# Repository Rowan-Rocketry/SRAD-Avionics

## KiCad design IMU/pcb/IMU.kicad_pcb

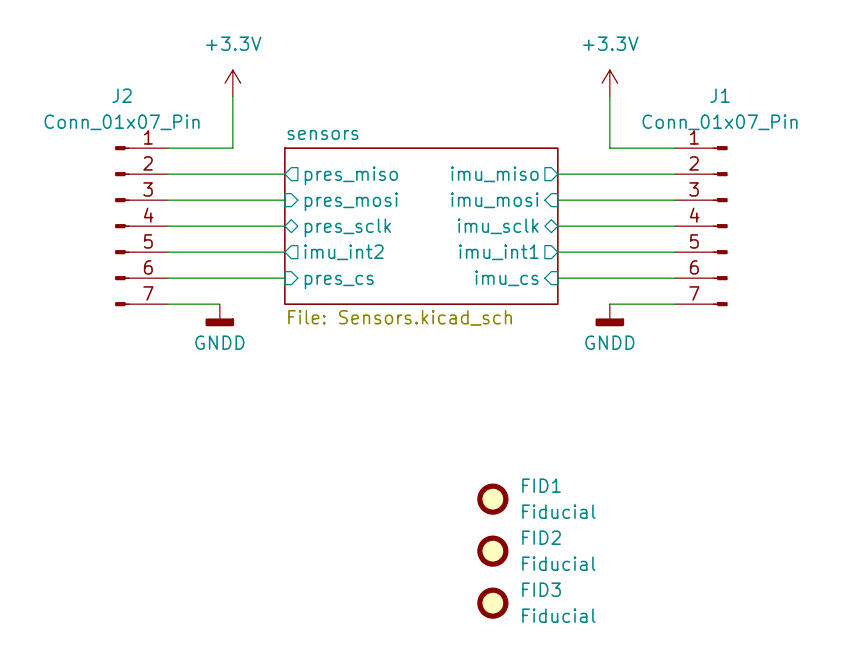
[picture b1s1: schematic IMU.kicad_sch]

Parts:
FID1, FID2, FID3: Fiducial; Fiducial_1mm_Mask2mm
J1, J2: Conn_01x07_Pin; PinHeader_1x07_P2.54mm_Vertical

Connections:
+3.3V: J1.1, J2.1; also elsewhere on the board
/sensors/imu_cs: J1.6; also elsewhere on the board
/sensors/imu_int1: J1.5; also elsewhere on the board
/sensors/imu_int2: J2.5; also elsewhere on the board
/sensors/imu_miso: J1.2; also elsewhere on the board
/sensors/imu_mosi: J1.3; also elsewhere on the board
/sensors/imu_sclk: J1.4; also elsewhere on the board
/sensors/pres_cs: J2.6; also elsewhere on the board
/sensors/pres_miso: J2.2; also elsewhere on the board
/sensors/pres_mosi: J2.3; also elsewhere on the board
/sensors/pres_sclk: J2.4; also elsewhere on the board
GNDD: J1.7, J2.7; also elsewhere on the board

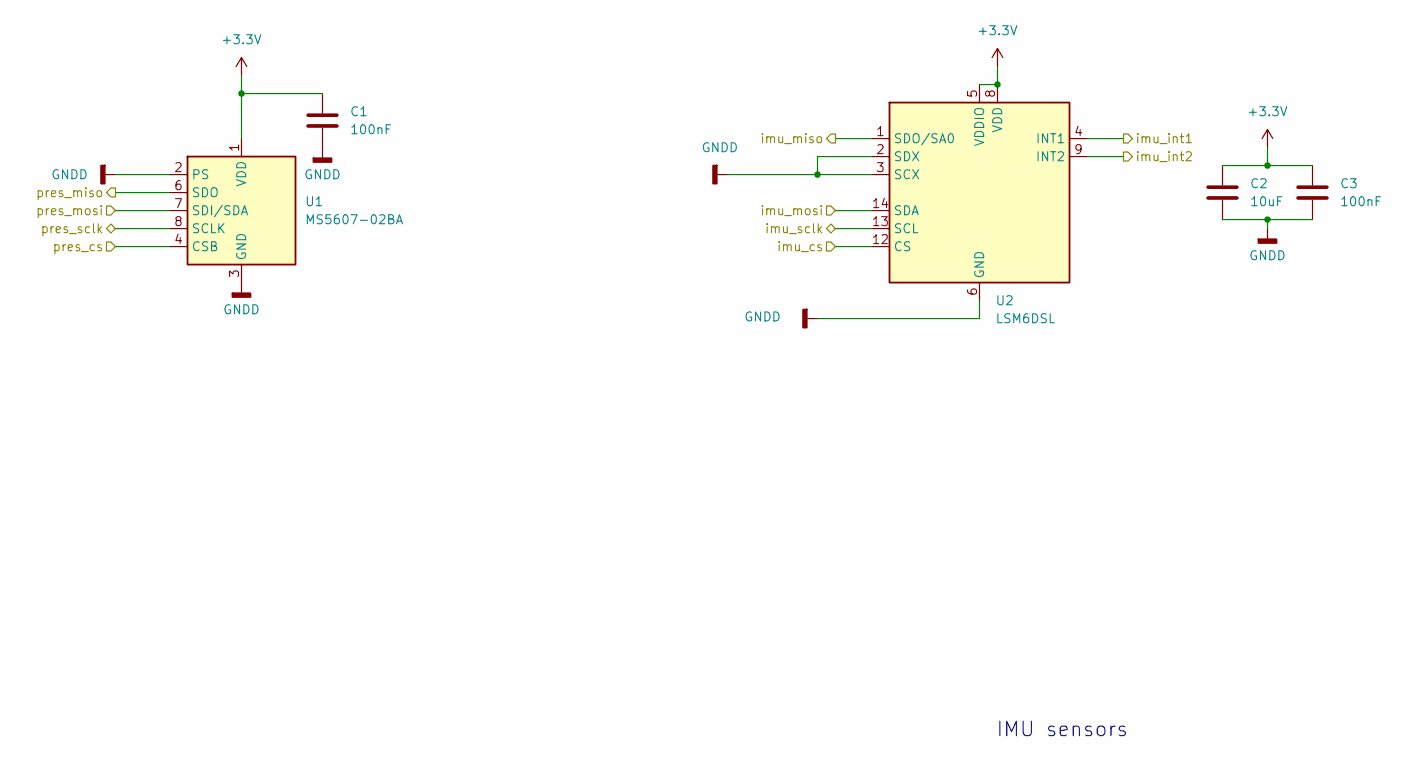
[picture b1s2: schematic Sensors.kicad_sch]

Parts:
C1, C3: 100nF; C_0603_1608Metric_Pad1.08x0.95mm_HandSolder
C2: 10uF; C_0603_1608Metric_Pad1.08x0.95mm_HandSolder
U1: MS5607-02BA; LGA-8_3x5mm_P1.25mm
U2: LSM6DSL; LGA-14_3x2.5mm_P0.5mm_LayoutBorder3x4y

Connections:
+3.3V: C1.1, C2.1, C3.1, U1.1 (VDD), U2.5 (VDDIO), U2.8 (VDD); also elsewhere on the board
/sensors/imu_cs: U2.12 (CS); also elsewhere on the board
/sensors/imu_int1: U2.4 (INT1); also elsewhere on the board
/sensors/imu_int2: U2.9 (INT2); also elsewhere on the board
/sensors/imu_miso: U2.1 (SDO/SA0); also elsewhere on the board
/sensors/imu_mosi: U2.14 (SDA); also elsewhere on the board
/sensors/imu_sclk: U2.13 (SCL); also elsewhere on the board
/sensors/pres_cs: U1.4 (CSB), U1.5 (CSB); also elsewhere on the board
/sensors/pres_miso: U1.6 (SDO); also elsewhere on the board
/sensors/pres_mosi: U1.7 (SDI/SDA); also elsewhere on the board
/sensors/pres_sclk: U1.8 (SCLK); also elsewhere on the board
GNDD: C1.2, C2.2, C3.2, U1.2 (PS), U1.3 (GND), U2.2 (SDX), U2.3 (SCX), U2.6 (GND), U2.7 (GND); also elsewhere on the board

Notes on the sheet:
IMU sensors

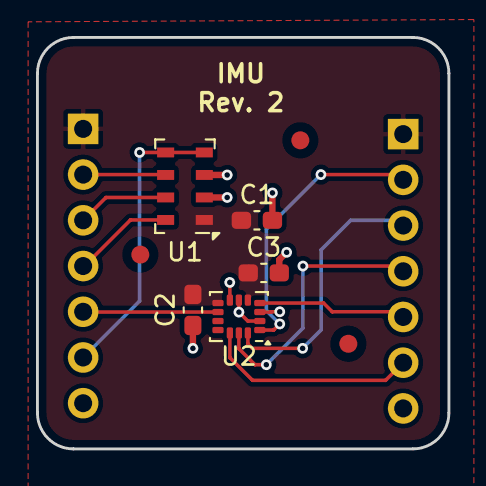
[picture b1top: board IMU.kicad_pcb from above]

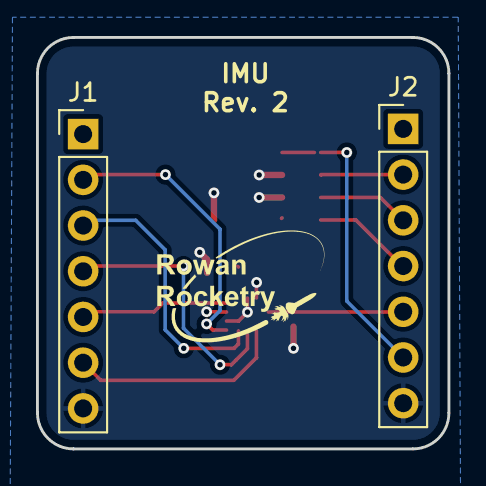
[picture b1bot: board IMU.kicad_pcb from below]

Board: 2 copper layers, 22.9 x 22.9 mm, 10 parts (2 on the bottom side), 12 nets.

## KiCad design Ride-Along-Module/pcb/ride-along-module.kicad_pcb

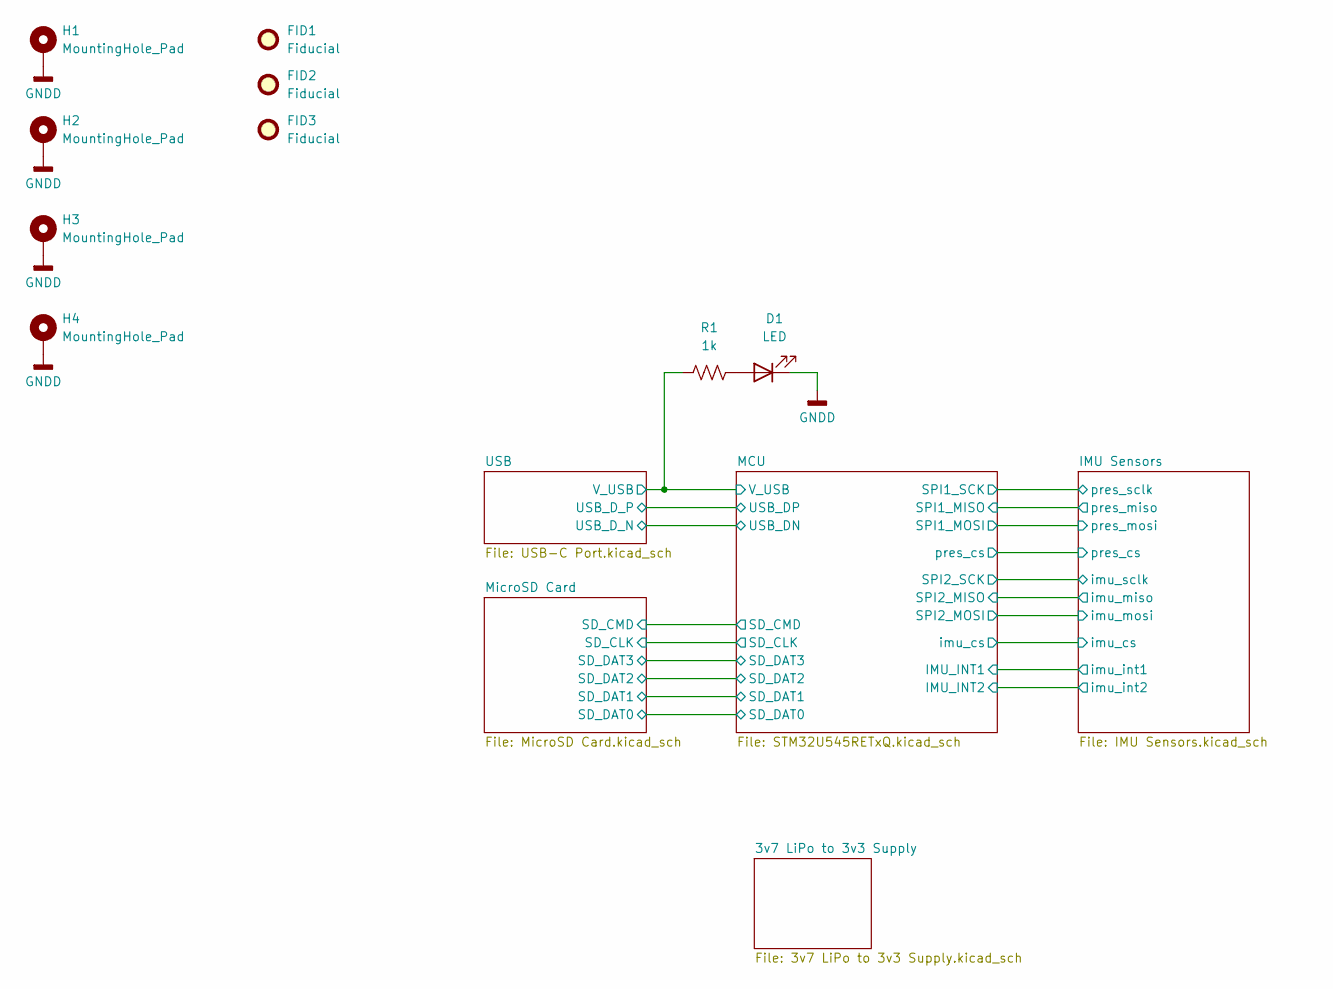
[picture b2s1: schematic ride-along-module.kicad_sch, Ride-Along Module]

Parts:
D1: LED; LED_0603_1608Metric
FID1, FID2, FID3: Fiducial; Fiducial_1mm_Mask3mm
H1, H2, H3, H4: MountingHole_Pad; MountingHole_3.2mm_M3_Pad_Via
R1: 1k; R_0603_1608Metric

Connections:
/MCU/VDDUSB: R1.1; also elsewhere on the board
GNDD: D1.1 (K), H1.1, H2.1, H3.1, H4.1; also elsewhere on the board
unnamed: D1.2 (A), R1.2

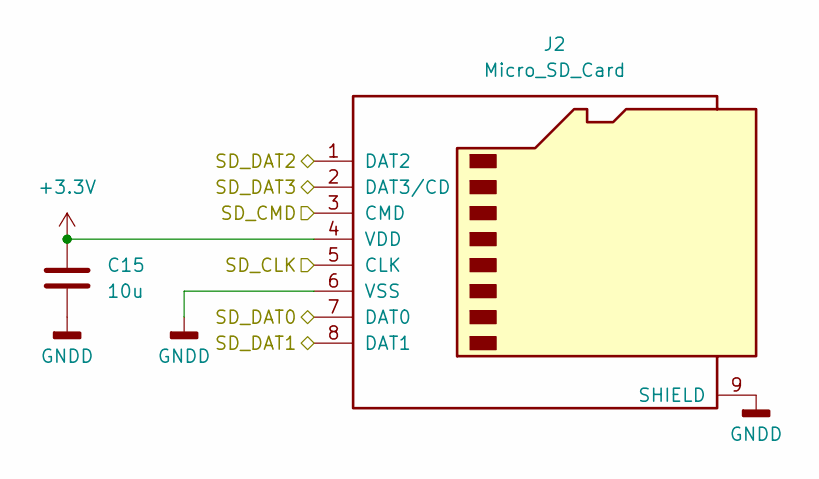
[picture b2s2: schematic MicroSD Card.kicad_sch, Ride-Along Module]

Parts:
C15: 10u; C_0603_1608Metric
J2: Micro_SD_Card; microSD_HC_Molex_47219-2001

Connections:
+3.3V: C15.1, J2.4 (VDD); also elsewhere on the board
/MCU/SD_CLK: J2.5 (CLK); also elsewhere on the board
/MCU/SD_CMD: J2.3 (CMD); also elsewhere on the board
/MCU/SD_DAT0: J2.7 (DAT0); also elsewhere on the board
/MCU/SD_DAT1: J2.8 (DAT1); also elsewhere on the board
/MCU/SD_DAT2: J2.1 (DAT2); also elsewhere on the board
/MCU/SD_DAT3: J2.2 (DAT3/CD); also elsewhere on the board
GNDD: C15.2, J2.6 (VSS), J2.9 (SHIELD); also elsewhere on the board

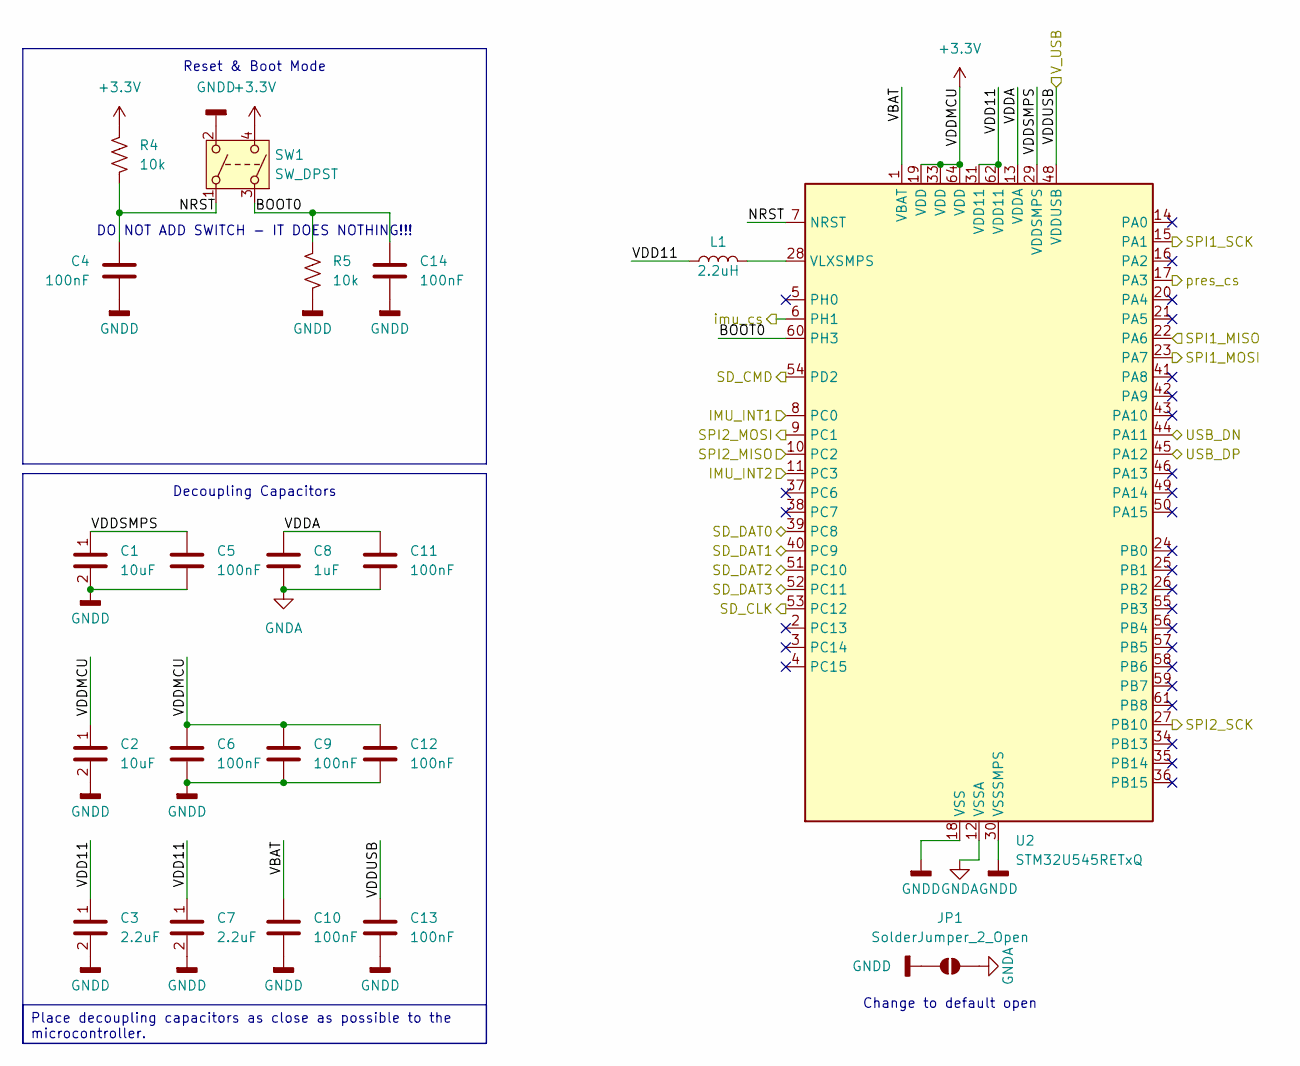
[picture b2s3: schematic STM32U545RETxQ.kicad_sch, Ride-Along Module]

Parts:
C1, C2: 10uF; C_0402_1005Metric
C3, C7: 2.2uF; C_0402_1005Metric
C4, C14: 100nF; C_0603_1608Metric
C5, C6, C9, C10, C11, C12, C13: 100nF; C_0402_1005Metric
C8: 1uF; C_0402_1005Metric
JP1: SolderJumper_2_Open; SolderJumper-2_P1.3mm_Open_RoundedPad1.0x1.5mm
L1: 2.2uH; L_0402_1005Metric
R4, R5: 10k; R_0603_1608Metric
SW1: SW_DPST; SW_DIP_SPSTx02_Slide_Copal_CHS-02A_W5.08mm_P1.27mm_JPin
U2: STM32U545RETxQ; LQFP-64_10x10mm_P0.5mm

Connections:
+3.3V: C2.1, C6.1, C9.1, C12.1, R4.1, SW1.4, U2.19 (VDD), U2.33 (VDD), U2.64 (VDD); also elsewhere on the board
/IMU Sensors/imu_cs: U2.6 (PH1); also elsewhere on the board
/IMU Sensors/imu_int1: U2.8 (PC0); also elsewhere on the board
/IMU Sensors/imu_int2: U2.11 (PC3); also elsewhere on the board
/IMU Sensors/imu_miso: U2.10 (PC2); also elsewhere on the board
/IMU Sensors/imu_mosi: U2.9 (PC1); also elsewhere on the board
/IMU Sensors/imu_sclk: U2.27 (PB10); also elsewhere on the board
/IMU Sensors/pres_cs: U2.17 (PA3); also elsewhere on the board
/IMU Sensors/pres_miso: U2.22 (PA6); also elsewhere on the board
/IMU Sensors/pres_mosi: U2.23 (PA7); also elsewhere on the board
/IMU Sensors/pres_sclk: U2.15 (PA1); also elsewhere on the board
/MCU/BOOT0: C14.2, R5.1, SW1.3, U2.60 (PH3)
/MCU/NRST: C4.2, R4.2, SW1.1, U2.7 (NRST)
/MCU/SD_CLK: U2.53 (PC12); also elsewhere on the board
/MCU/SD_CMD: U2.54 (PD2); also elsewhere on the board
/MCU/SD_DAT0: U2.39 (PC8); also elsewhere on the board
/MCU/SD_DAT1: U2.40 (PC9); also elsewhere on the board
/MCU/SD_DAT2: U2.51 (PC10); also elsewhere on the board
/MCU/SD_DAT3: U2.52 (PC11); also elsewhere on the board
/MCU/USB_DN: U2.44 (PA11); also elsewhere on the board
/MCU/USB_DP: U2.45 (PA12); also elsewhere on the board
/MCU/VBAT: C10.1, U2.1 (VBAT)
/MCU/VDD11: C3.1, C7.1, L1.1, U2.31 (VDD11), U2.62 (VDD11)
/MCU/VDDA: C8.1, C11.1, U2.13 (VDDA)
/MCU/VDDSMPS: C1.1, C5.1, U2.29 (VDDSMPS)
/MCU/VDDUSB: C13.1, U2.48 (VDDUSB); also elsewhere on the board
GNDA: C8.2, C11.2, JP1.2 (B), U2.12 (VSSA)
GNDD: C1.2, C2.2, C3.2, C4.1, C5.2, C6.2, C7.2, C9.2, C10.2, C12.2, C13.2, C14.1, JP1.1 (A), R5.2, SW1.2, U2.18 (VSS), U2.30 (VSSSMPS), U2.32 (VSS), U2.47 (VSS), U2.63 (VSS); also elsewhere on the board
unnamed: L1.2, U2.28 (VLXSMPS)

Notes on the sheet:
Decoupling Capacitors
Reset & Boot Mode
Change to default open
DO NOT ADD SWITCH - IT DOES NOTHING!!!
Place decoupling capacitors as close as possible to the microcontroller.

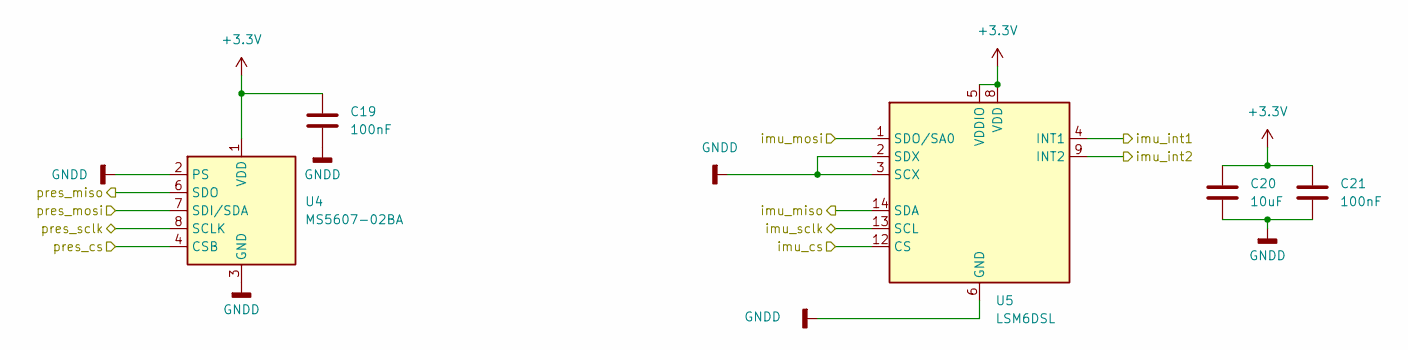
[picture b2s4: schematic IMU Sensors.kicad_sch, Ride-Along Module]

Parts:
C19, C21: 100nF; C_0603_1608Metric
C20: 10uF; CP_EIA-3216-18_Kemet-A
U4: MS5607-02BA; LGA-8_3x5mm_P1.25mm
U5: LSM6DSL; LGA-14_3x2.5mm_P0.5mm_LayoutBorder3x4y

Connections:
+3.3V: C19.1, C20.1, C21.1, U4.1 (VDD), U5.5 (VDDIO), U5.8 (VDD); also elsewhere on the board
/IMU Sensors/imu_cs: U5.12 (CS); also elsewhere on the board
/IMU Sensors/imu_int1: U5.4 (INT1); also elsewhere on the board
/IMU Sensors/imu_int2: U5.9 (INT2); also elsewhere on the board
/IMU Sensors/imu_miso: U5.14 (SDA); also elsewhere on the board
/IMU Sensors/imu_mosi: U5.1 (SDO/SA0); also elsewhere on the board
/IMU Sensors/imu_sclk: U5.13 (SCL); also elsewhere on the board
/IMU Sensors/pres_cs: U4.4 (CSB), U4.5 (CSB); also elsewhere on the board
/IMU Sensors/pres_miso: U4.6 (SDO); also elsewhere on the board
/IMU Sensors/pres_mosi: U4.7 (SDI/SDA); also elsewhere on the board
/IMU Sensors/pres_sclk: U4.8 (SCLK); also elsewhere on the board
GNDD: C19.2, C20.2, C21.2, U4.2 (PS), U4.3 (GND), U5.2 (SDX), U5.3 (SCX), U5.6 (GND), U5.7 (GND); also elsewhere on the board

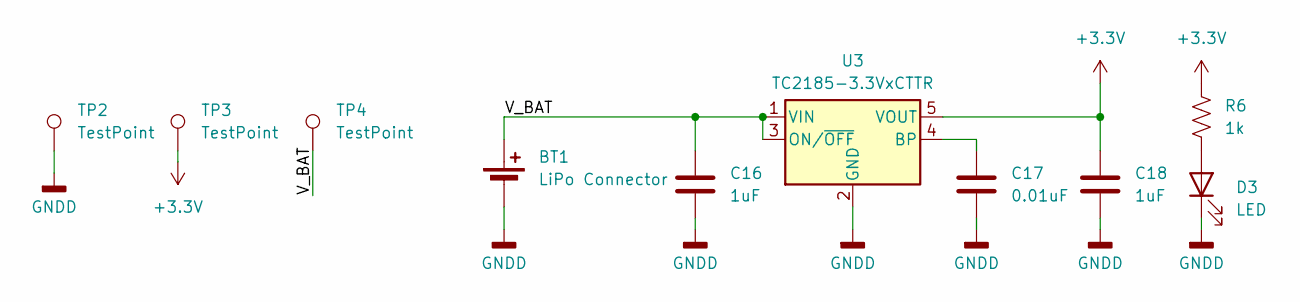
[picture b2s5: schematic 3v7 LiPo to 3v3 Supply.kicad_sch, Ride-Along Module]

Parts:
BT1: LiPo Connector; JST_PH_B2B-PH-K_1x02_P2.00mm_Vertical
C16, C18: 1uF; C_0603_1608Metric
C17: 0.01uF; C_0603_1608Metric
D3: LED; LED_0603_1608Metric
R6: 1k; R_0603_1608Metric
TP2, TP3, TP4: TestPoint; TestPoint_Loop_D2.60mm_Drill1.6mm_Beaded
U3: TC2185-3.3VxCTTR; SOT-23-5

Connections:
+3.3V: C18.1, R6.1, TP3.1, U3.5 (VOUT); also elsewhere on the board
/3v7 LiPo to 3v3 Supply/V_BAT: BT1.1 (+), C16.1, TP4.1, U3.1 (VIN), U3.3 (ON/~OFF)
GNDD: BT1.2 (-), C16.2, C17.2, C18.2, D3.1 (K), TP2.1, U3.2 (GND); also elsewhere on the board
unnamed: D3.2 (A), R6.2
unnamed: C17.1, U3.4 (BP)

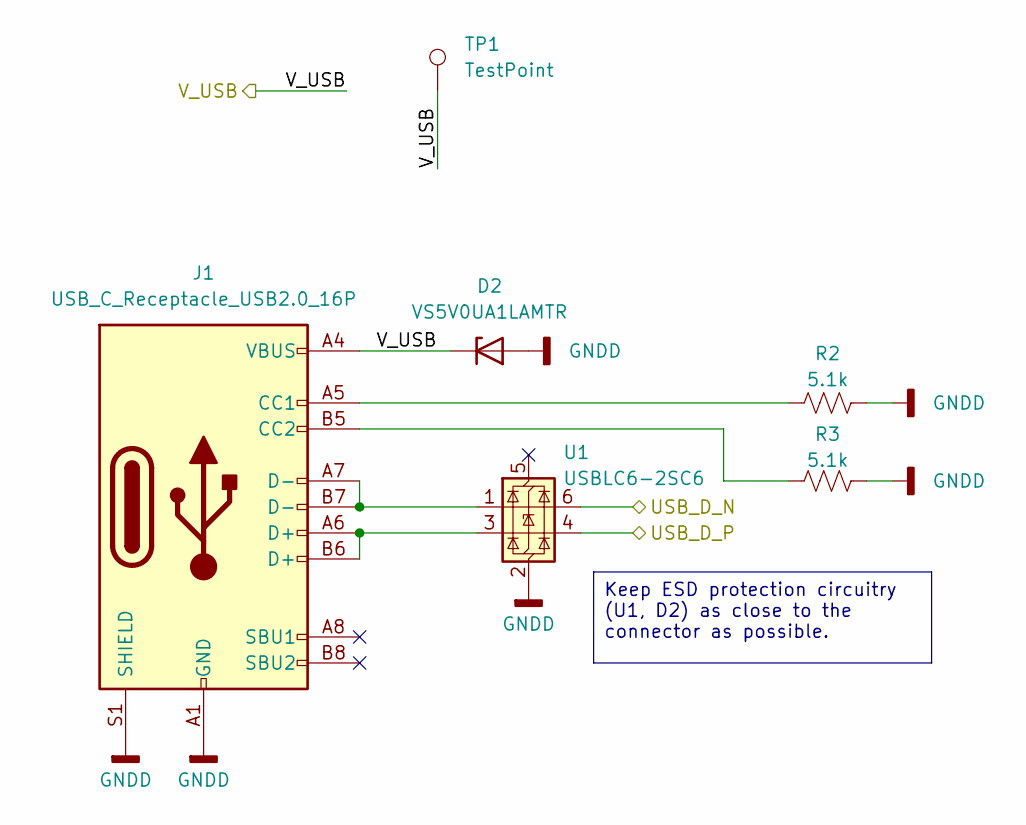
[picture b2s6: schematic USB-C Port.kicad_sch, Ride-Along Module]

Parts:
D2: VS5V0UA1LAMTR; D_SOD-128
J1: USB_C_Receptacle_USB2.0_16P; USB_C_Receptacle_GCT_USB4105-xx-A_16P_TopMnt_Horizontal
R2, R3: 5.1k; R_0603_1608Metric
TP1: TestPoint; TestPoint_Loop_D2.60mm_Drill1.6mm_Beaded
U1: USBLC6-2SC6; SOT-23-6

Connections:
/MCU/USB_DN: U1.6 (I/O1); also elsewhere on the board
/MCU/USB_DP: U1.4 (I/O2); also elsewhere on the board
/MCU/VDDUSB: D2.1 (K), J1.A4 (VBUS), J1.A9 (VBUS), J1.B4 (VBUS), J1.B9 (VBUS), TP1.1; also elsewhere on the board
GNDD: D2.2 (A), J1.A1 (GND), J1.A12 (GND), J1.B1 (GND), J1.B12 (GND), J1.S1 (SHIELD), R2.2, R3.2, U1.2 (GND); also elsewhere on the board
unnamed: J1.A5 (CC1), R2.1
unnamed: J1.B5 (CC2), R3.1
unnamed: J1.A6 (D+), J1.B6 (D+), U1.3 (I/O2)
unnamed: J1.A7 (D-), J1.B7 (D-), U1.1 (I/O1)

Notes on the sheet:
Keep ESD protection circuitry (U1, D2) as close to the connector as possible.

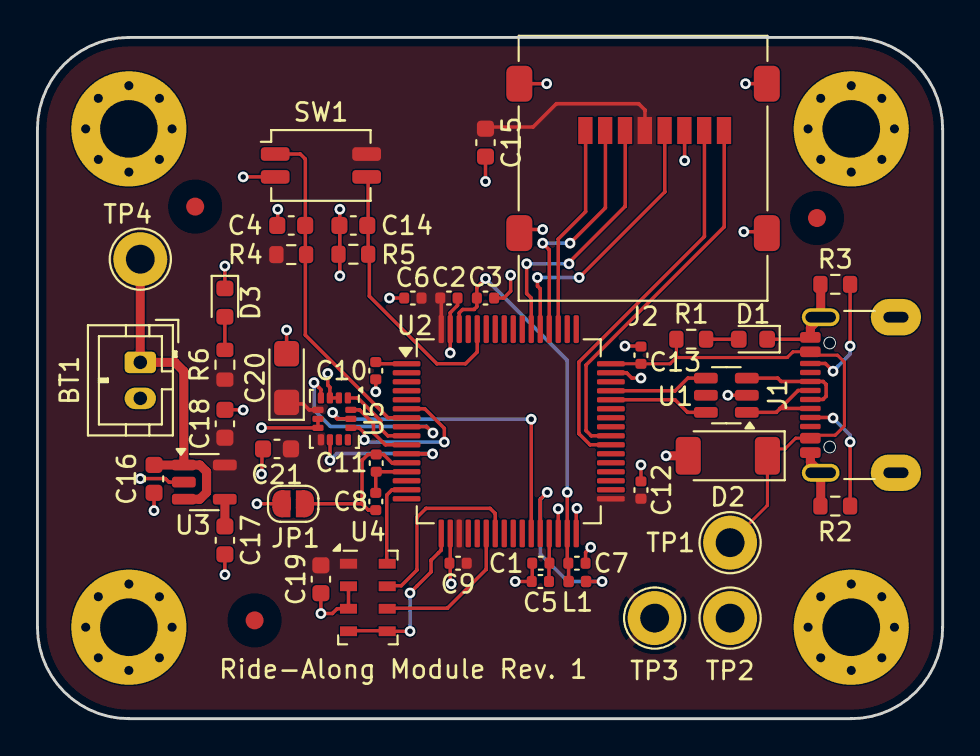
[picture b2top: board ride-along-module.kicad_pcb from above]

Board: 2 copper layers, 50.3 x 37.8 mm, 52 parts (0 on the bottom side), 37 nets.

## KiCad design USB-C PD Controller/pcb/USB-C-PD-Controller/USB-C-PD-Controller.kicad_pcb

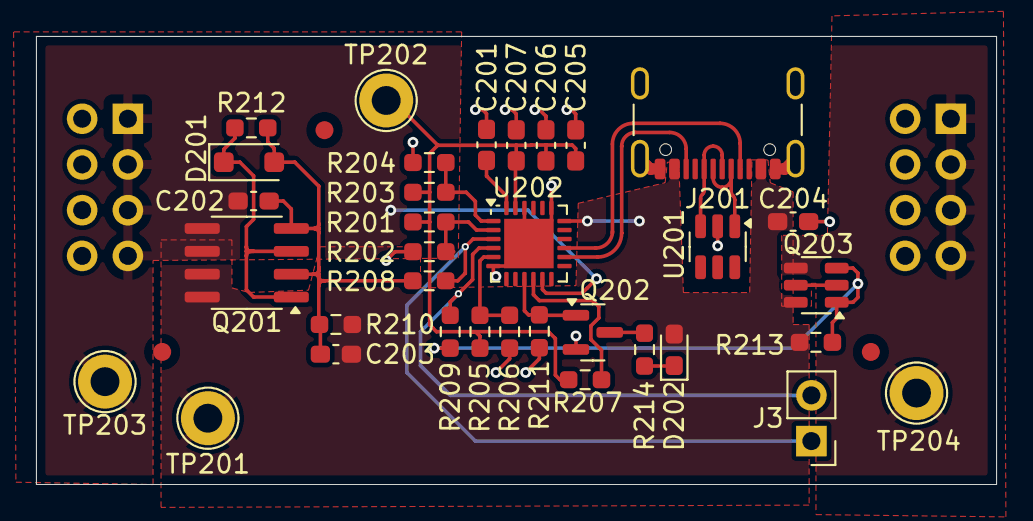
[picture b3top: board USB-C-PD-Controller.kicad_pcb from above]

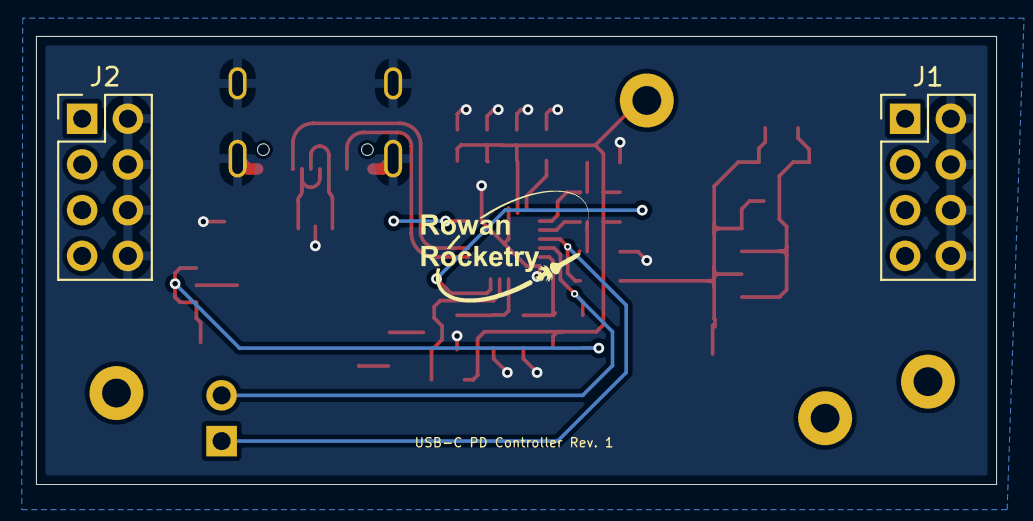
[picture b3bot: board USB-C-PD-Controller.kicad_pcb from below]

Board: 2 copper layers, 53.3 x 24.9 mm, 39 parts (2 on the bottom side), 23 nets.

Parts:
C201, C202, C203, C205: 1u; C_0603_1608Metric_Pad1.08x0.95mm_HandSolder
C204: 3.3u; C_0603_1608Metric_Pad1.08x0.95mm_HandSolder
C206, C207: 0.1u; C_0603_1608Metric_Pad1.08x0.95mm_HandSolder
D201: NZH10C,115; D_SOD-123F
D202: 150060AS75000; LED_0603_1608Metric_Pad1.05x0.95mm_HandSolder
FID1, FID2, FID3: Fiducial; Fiducial_1mm_Mask2mm
J1, J2: Conn_02x04_Odd_Even; PinHeader_2x04_P2.54mm_Vertical
J3: Conn_01x02_Pin; PinHeader_1x02_P2.54mm_Vertical
J201: USB_C_Receptacle_USB2.0_16P; USB_C_Receptacle_GCT_USB4105-xx-A_16P_TopMnt_Horizontal
Q201: IRF9358; SOIC-8_3.9x4.9mm_P1.27mm
Q202: 2N7002; SOT-23
Q203: BSL308PE; TSOT-23-6
R201, R202, R203, R204, R205, R206: 5.1k; R_0603_1608Metric_Pad0.98x0.95mm_HandSolder
R207: 4.7k; R_0603_1608Metric_Pad0.98x0.95mm_HandSolder
R208, R209, R214: 1k; R_0603_1608Metric_Pad0.98x0.95mm_HandSolder
R210: 10k; R_0603_1608Metric_Pad0.98x0.95mm_HandSolder
R211: 100k; R_0603_1608Metric_Pad0.98x0.95mm_HandSolder
R212, R213: 49.9k; R_0603_1608Metric_Pad0.98x0.95mm_HandSolder
TP201, TP202, TP203, TP204: TestPoint; TestPoint_Loop_D2.60mm_Drill1.6mm_Beaded
U201: USBLC6-2SC6; SOT-23-6
U202: CYPD3177-24LQ; QFN-24-1EP_4x4mm_P0.5mm_EP2.75x2.75mm

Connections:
+5V: J2.1, J2.3, J2.5, J2.7, Q203.4 (D2), TP204.1
+15V: C202.1, J1.1, J1.3, J1.5, J1.7, Q201.5 (D2), Q201.6 (D2), TP203.1, U202.11 (VDC_OUT)
/USB-C PD Controller/CC1: J201.A5 (CC1), U202.15 (CC1)
/USB-C PD Controller/CC2: J201.B5 (CC2), U202.14 (CC2)
/USB-C PD Controller/ISNK_COARSE: R205.2, R206.1, U202.5 (ISNK_COARSE)
/USB-C PD Controller/SAFE_PWR_EN: J3.2, R209.2, U202.4 (SAFE_PWR_EN)
/USB-C PD Controller/VBUS_FET_EN: J3.1, R208.1, U202.3 (VBUS_FET_EN)
/USB-C PD Controller/VBUS_MAX: R201.2, R202.1, U202.2 (VBUS_MAX)
/USB-C PD Controller/VBUS_MIN: R203.2, R204.1, U202.1 (VBUS_MIN)
/USB-C PD Controller/VDDD: C205.2, C206.2, C207.2, R201.1, R203.1, R205.1, R207.1, TP202.1, U202.23 (VDDD)
/USB-C PD Controller/V_USB: C203.1, C204.1, D202.2 (A), J201.A4 (VBUS), J201.A9 (VBUS), J201.B4 (VBUS), J201.B9 (VBUS), Q201.7 (D1), Q201.8 (D1), Q203.6 (D1), R210.1, R213.1, TP201.1, U202.18 (VBUS_IN)
GNDD: C201.1, C204.2, C205.1, C206.1, C207.1, J1.2, J1.4, J1.6, J1.8, J2.2, J2.4, J2.6, J2.8, J201.A1 (GND), J201.A12 (GND), J201.B1 (GND), J201.B12 (GND), J201.S1 (SHIELD), Q202.2 (S), R202.2, R204.2, R206.2, R211.2, U201.2 (GND), U202.6 (ISNK_FINE), U202.19 (GND), U202.22 (GND), U202.25 (GND)
unnamed: C202.2, C203.2, D201.2 (A), Q201.2 (G1), Q201.4 (G2), R208.2, R210.2, R212.2
unnamed: D201.1 (K), Q201.1 (S1), Q201.3 (S2), R212.1
unnamed: D202.1 (K), R214.1
unnamed: J201.A6 (D+), J201.B6 (D+), U201.3 (I/O2)
unnamed: J201.A7 (D-), J201.B7 (D-), U201.1 (I/O1)
unnamed: Q202.3 (D), R214.2
unnamed: Q202.1 (G), R211.1, U202.9 (FAULT)
unnamed: Q203.1 (G1), Q203.3 (G2), R209.1, R213.2
unnamed: Q203.2 (S2), Q203.5 (S1)
unnamed: R207.2, U202.10 (FLIP)
unnamed: C201.2, U202.24 (VCCD)

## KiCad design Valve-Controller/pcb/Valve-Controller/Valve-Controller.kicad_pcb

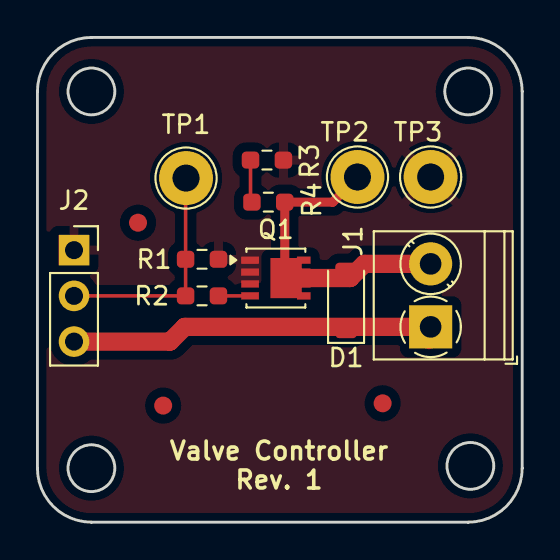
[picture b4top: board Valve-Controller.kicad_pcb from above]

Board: 2 copper layers, 26.9 x 26.9 mm, 14 parts (0 on the bottom side), 6 nets.

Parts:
D1: D; D_SOD-123
FID1, FID2, FID3: Fiducial; Fiducial_1mm_Mask2mm
J1: Screw_Terminal_01x02; TerminalBlock_Phoenix_PT-1,5-2-3.5-H_1x02_P3.50mm_Horizontal
J2: Conn_01x03_Socket; PinSocket_1x03_P2.54mm_Vertical
Q1: SiS454DN; Vishay_PowerPAK_1212-8_Single
R1: 3.3K; R_0603_1608Metric_Pad0.98x0.95mm_HandSolder
R2: 1K; R_0603_1608Metric_Pad0.98x0.95mm_HandSolder
R3: 100K; R_0603_1608Metric_Pad0.98x0.95mm_HandSolder
R4: 27K; R_0603_1608Metric_Pad0.98x0.95mm_HandSolder
TP1, TP2, TP3: TestPoint; TestPoint_Loop_D2.54mm_Drill1.5mm_Beaded

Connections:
+12V: D1.1 (K), J1.1, J2.3
/ValveController/Input: J2.2, R1.2, R2.1, TP1.1
/ValveController/Output: D1.2 (A), J1.2, Q1.5 (D), R3.1, TP2.1
GNDD: J2.1, Q1.1 (S), Q1.2 (S), Q1.3 (S), R1.1, R4.1, TP3.1
unnamed: Q1.4 (G), R2.2
unnamed: R3.2, R4.2

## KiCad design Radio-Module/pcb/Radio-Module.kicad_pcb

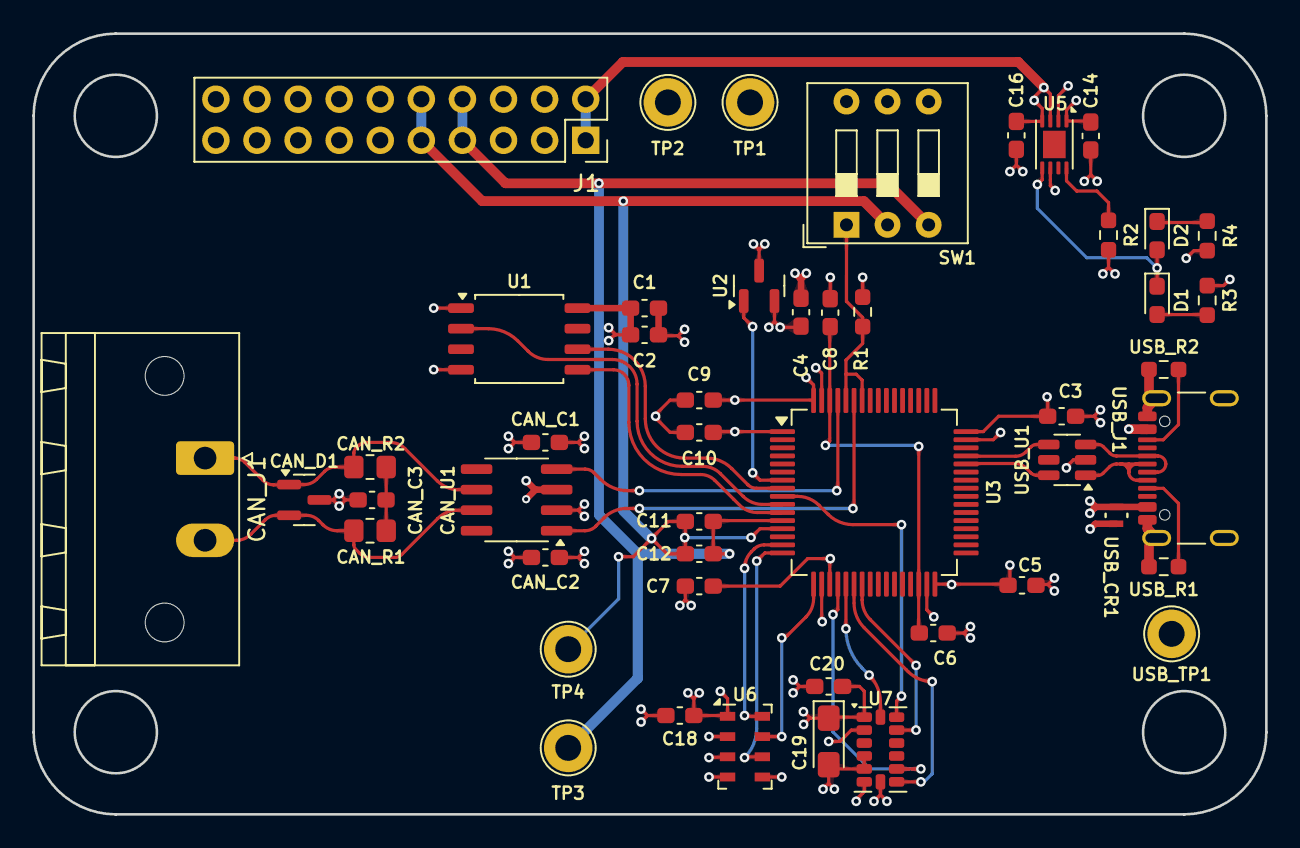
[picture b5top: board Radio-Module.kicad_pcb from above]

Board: 4 copper layers, 76.2 x 48.3 mm, 49 parts (0 on the bottom side), 35 nets.

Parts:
C1, C3, C4, C5, C7, C9, C11, C18, C20: 100nF; C_0603_1608Metric_Pad1.08x0.95mm_HandSolder
C2, C10, C14, C16: 4.7uF; C_0603_1608Metric_Pad1.08x0.95mm_HandSolder
C6, C8: 2.2uF; C_0603_1608Metric_Pad1.08x0.95mm_HandSolder
C12: 1uF; C_0603_1608Metric_Pad1.08x0.95mm_HandSolder
C19: 10uF; CP_EIA-3216-18_Kemet-A_Pad1.58x1.35mm_HandSolder
CAN_C1: 100nF; C_0603_1608Metric_Pad1.08x0.95mm_HandSolder
CAN_C2, CAN_C3: 4.7uF; C_0603_1608Metric_Pad1.08x0.95mm_HandSolder
CAN_D1: NUP2105L; SOT-23
CAN_J1: Conn_01x02_Socket; PhoenixContact_MSTB_2,5_2-GF-5,08_1x02_P5.08mm_Horizontal_T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
CAN_R1, CAN_R2: 62; R_0805_2012Metric_Pad1.20x1.40mm_HandSolder
CAN_U1: TCAN332G; SOIC-8_3.9x4.9mm_P1.27mm
D1, D2: LED; LED_0603_1608Metric_Pad1.05x0.95mm_HandSolder
J1: Conn_02x10_Odd_Even; PinSocket_2x10_P2.54mm_Vertical
R1: 10k; R_0603_1608Metric_Pad0.98x0.95mm_HandSolder
R2: 2k; R_0603_1608Metric_Pad0.98x0.95mm_HandSolder
R3, R4: 1k; R_0603_1608Metric_Pad0.98x0.95mm_HandSolder
SW1: SW_DIP_x03; SW_DIP_SPSTx03_Slide_9.78x9.8mm_W7.62mm_P2.54mm
TP1, TP2, TP3, TP4: TestPoint; TestPoint_Loop_D2.60mm_Drill1.6mm_Beaded
U1: W25Q128JVS; SOIC-8_5.23x5.23mm_P1.27mm
U2: MCP130-xxxxTT; SOT-23
U3: STM32H503RBTx; LQFP-64_10x10mm_P0.5mm
U5: MCP73831-2-MC; DFN-8-1EP_3x2mm_P0.5mm_EP1.7x1.4mm
U6: MS5607-02BA; LGA-8_3x5mm_P1.25mm
U7: ADXL375BCCZ; LGA-14_3x5mm_P0.8mm_LayoutBorder1x6y
USB_CR1: ESDA7P60-1U1M; ZDO_1610_STM
USB_J1: USB_C_Receptacle_USB2.0_16P; USB_C_Receptacle_GCT_USB4105-xx-A_16P_TopMnt_Horizontal
USB_R1, USB_R2: 5.1k; R_0603_1608Metric_Pad0.98x0.95mm_HandSolder
USB_TP1: TestPoint; TestPoint_Loop_D2.60mm_Drill1.6mm_Beaded
USB_U1: USBLC6-2SC6; SOT-23-6

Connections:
+3.3V: C1.1, C2.1, C3.1, C4.1, C5.1, C7.1, C9.1, C10.1, C18.1, C19.1, C20.1, CAN_C1.1, CAN_C2.1, CAN_U1.3 (VCC), J1.5, J1.6, SW1.5, SW1.6, TP1.1, U1.8 (VCC), U2.2 (VDD), U3.1 (VBAT), U3.19 (VDD), U3.32 (VDD), U3.48 (VDD), U3.64 (VDD), U6.1 (VDD), U7.1 (VDD_I/O), U7.6 (VS)
/BOOT0: R1.1, SW1.1, U3.58 (PB6), U3.60 (BOOT0)
/Battery Management/STAT: D1.1 (K), D2.2 (A), U5.5 (STAT)
/Battery Management/V_USB: C14.1, R3.2, U5.1 (V_{DD}), U5.2 (V_{DD}), USB_CR1.1, USB_J1.A4 (VBUS), USB_J1.A9 (VBUS), USB_J1.B4 (VBUS), USB_J1.B9 (VBUS), USB_TP1.1
/CAN Interface/CAN_H: CAN_D1.2 (K), CAN_J1.2, CAN_R1.1, CAN_U1.7 (CANH)
/CAN Interface/CAN_L: CAN_D1.1 (K), CAN_J1.1, CAN_R2.2, CAN_U1.6 (CANL)
/FDCAN_RX: CAN_U1.4 (RXD), U3.61 (PB8)
/FDCAN_TX: CAN_U1.1 (TXD), U3.59 (PB7)
/USB_D_N: U3.44 (PA11), USB_U1.6 (I/O1)
/USB_D_P: U3.45 (PA12), USB_U1.4 (I/O2)
/V_BAT: C16.1, J1.1, J1.2, U5.3 (V_{BAT}), U5.4 (V_{BAT})
/accel_clk: U3.21 (PA5), U7.14 (SCL/SCLK)
/accel_int1: U3.20 (PA4), U7.9 (INT2)
/accel_int2: U3.22 (PA6), U7.8 (INT1)
/accel_miso: U3.23 (PA7), U7.12 (SDO/ALT_ADDRESS)
/accel_mosi: U3.9 (PC1), U7.13 (SDA/SDI/SDIO)
/flash_clk: U1.6 (CLK), U3.8 (PC0)
/flash_miso: U1.2 (DO(IO1)), U3.10 (PC2)
/flash_mosi: U1.5 (DI(IO0)), U3.11 (PC3)
/pres_clk: U3.15 (PA1), U6.8 (SCLK)
/pres_miso: U3.16 (PA2), U6.6 (SDO)
/pres_mosi: U3.17 (PA3), U6.7 (SDI/SDA)
GNDA: C11.2, C12.2, J1.7, J1.8, SW1.3, TP3.1, U3.12 (VSSA)
GNDD: C1.2, C2.2, C3.2, C4.2, C5.2, C6.2, C7.2, C8.2, C9.2, C10.2, C14.2, C16.2, C18.2, C19.2, C20.2, CAN_C1.2, CAN_C2.2, CAN_C3.2, CAN_D1.3 (A), CAN_U1.2 (GND), J1.3, J1.4, J1.19, J1.20, R1.2, R2.2, R4.2, SW1.4, TP2.1, U1.1 (~CS), U1.4 (GND), U2.3 (VSS), U3.18 (VSS), U3.31 (VSS), U3.47 (VSS), U3.63 (VSS), U5.6 (V_{SS}), U6.2 (PS), U6.3 (GND), U6.4 (CSB), U6.5 (CSB), U7.2 (GND), U7.4 (GND), U7.5 (GND), U7.7 (*CS), USB_CR1.2, USB_J1.A1 (GND), USB_J1.A12 (GND), USB_J1.B1 (GND), USB_J1.B12 (GND), USB_J1.S1 (SHIELD), USB_R1.2, USB_R2.2, USB_U1.2 (GND)
unnamed: C6.1, C8.1, U3.30 (VCAP), U3.62 (VCAP)
unnamed: CAN_C3.1, CAN_R1.2, CAN_R2.1
unnamed: D1.2 (A), R3.1
unnamed: D2.1 (K), R4.1
unnamed: U2.1 (~RST), U3.7 (NRST)
unnamed: R2.1, U5.8 (PROG)
unnamed: USB_J1.A5 (CC1), USB_R1.1
unnamed: USB_J1.B5 (CC2), USB_R2.1
unnamed: USB_J1.A6 (D+), USB_J1.B6 (D+), USB_U1.3 (I/O2)
unnamed: USB_J1.A7 (D-), USB_J1.B7 (D-), USB_U1.1 (I/O1)
VDDA: C11.1, C12.1, J1.9, J1.10, SW1.2, TP4.1, U3.13 (VDDA)

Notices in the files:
Ride-Along-Module/dev/ride-along-module/Core/Src/main.c:
Copyright (c) 2025 STMicroelectronics.
All rights reserved.
This software is licensed under terms that can be found in the LICENSE file
